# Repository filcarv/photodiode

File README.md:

# Photodiode

General photodiode to synchronize screens (or other light source) with behavior.

# Licensing

The code, designs, documentation, and photos available in this repository is free: you can redistribute it and/or modify it under the terms of the used license.
Each subdirectory will contain a license or, possibly, a set of licenses if it involves both hardware and software. Check files named LICENSE.

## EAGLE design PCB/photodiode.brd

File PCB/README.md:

# Photodiode

## Licensing

The designs, documentation, and photos available in this repository are free: you can redistribute it and/or modify it under the terms of the used license.
Check file named LICENSE.

Copyright Filipe Carvalho 2020-2021

<br />This work is licensed under a <a rel="license" href="http://creativecommons.org/licenses/by-nc-sa/3.0/igo/">Creative Commons Attribution-NonCommercial-ShareAlike 3.0 IGO License</a>.

If your are interested in obtaining a license to sell this device, please contact filipe@open-ephys.org

[1]: https://docs.google.com/spreadsheets/d/1aobmmEzBDethzIlrm1eg0eYkBqlyX3s9WbA9KgRwVQI/edit?usp=sharing

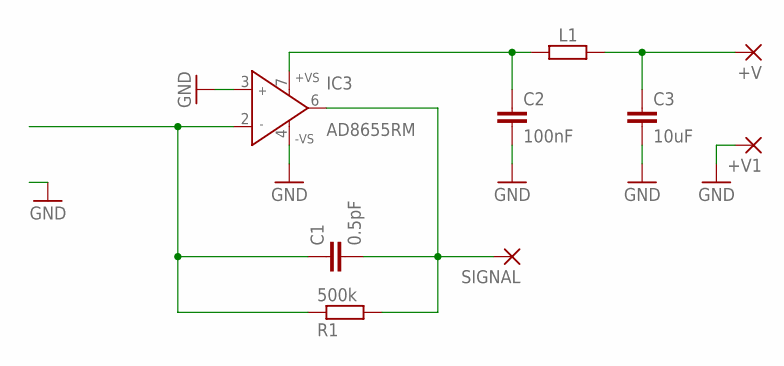
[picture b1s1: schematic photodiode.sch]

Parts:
+V, +V1: WIREPADSMD1,27-254; SMD1,27-2,54
C1: 0.5pF; C0402
C2: 100nF; C0402
C3: 10uF; C0603
IC3: AD8655RM; MSOP08
L1: 1k@100M; R0402
R1: 500k; R0402
SIGNAL: WIREPADSMD1,27-254; SMD1,27-2,54

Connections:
AMP_OUT: C1.2, IC3.6 (OUT), R1.2, SIGNAL.1
GND: +V1.1, C2.2, C3.2, IC3.3 (IN+), IC3.4 (-VS)
KATODE: C1.1, IC3.2 (IN-), R1.1
SUPPLY: C2.1, IC3.7 (+VS), L1.2
SUPPLY_INPUT: +V.1, C3.1, L1.1

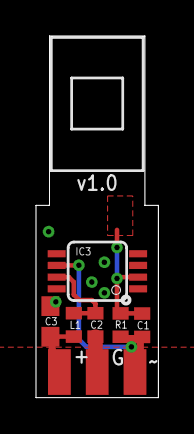
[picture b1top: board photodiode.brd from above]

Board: 2 copper layers, 6.8 x 20.1 mm, 9 parts (0 on the bottom side), 5 nets.

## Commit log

2021-03-01 Added PCB files and license.
2021-03-01 Added 3D files.
2021-03-01 Added some assembly photos.
2021-03-01 Updated README.md.
